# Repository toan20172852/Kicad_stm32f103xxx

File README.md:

# 1. Introduction
- Hi, I am Toan Nguyen, I learned how to using Kicad for design PCB from 1 week ago.
- I learn Kicad from some video in Youtube in [Phil'sLab](https://www.youtube.com/@PhilsLab), thank channel shared all Knowledge about Kicad for Work.
- This mini project is [course](https://www.udemy.com/course/learn-kicad-v6-and-stm32-hardware-design/learn/lecture/30585336#content) in Udemy of Phil'sLab is shared and free. If you have time, you can join the course.

# 2. Design Schematic
- **Total Schematic for STM32F103xxx**

- **Power supply:**

> I use [ASM117-3.3](https://pdf1.alldatasheet.com/datasheet-pdf/view/205691/ADMOS/AMS1117-3.3.html) as IC main for LDO voltage because:

> Current Output of ASM1117 suitable with 1A, Fixed Voltage is 3.3V for VDD of IC STM32F103.

>I using micro USB type B, current 10-100mA, Input voltage 5Vdc

>Now, we can see [example-ASM1117](https://www.pcboard.ca/ams1117-3-volt-regulator) of manafactory to design for this block:

> I using capacitor 0.1-10uF to filter input voltage, capacitor 47-1000uF to filter output voltage. LED is added to display Voltage 3.3V whether or not.

- **MCU**
> All design of MCU was referenced in internet with keyword "stm32f103c8 kit schematic", you can find schematic for this design with above keyword.

# 3. Layout
- **Layout**

- **3D**

---
---
**Goodluck!**

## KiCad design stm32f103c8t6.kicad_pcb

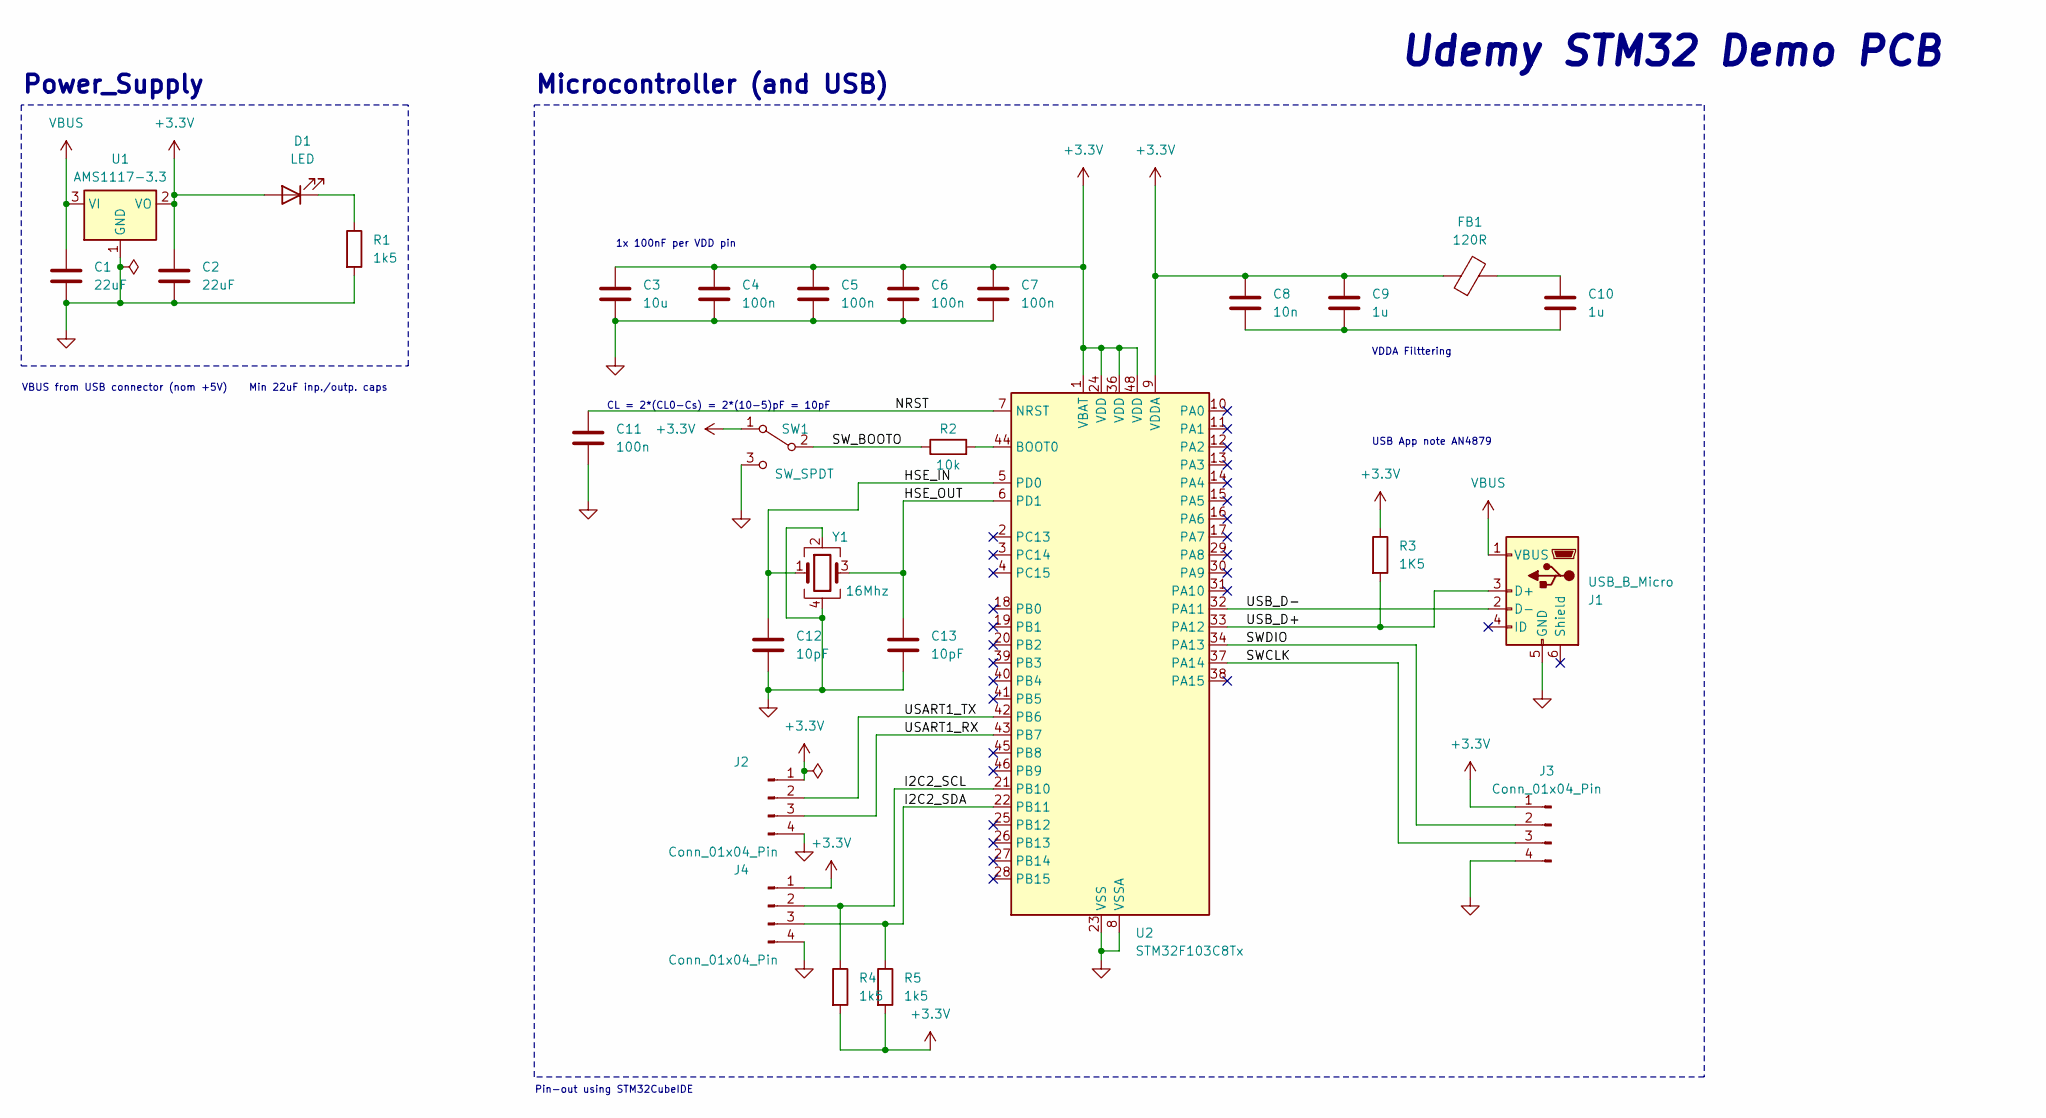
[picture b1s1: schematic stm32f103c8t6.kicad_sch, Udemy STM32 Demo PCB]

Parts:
C1, C2: 22uF; C_0805_2012Metric
C3: 10u; C_0805_2012Metric
C4, C5, C6, C7, C11: 100n; C_0402_1005Metric
C8: 10n; C_0402_1005Metric
C9, C10: 1u; C_0402_1005Metric
C12, C13: 10pF; C_0402_1005Metric
D1: LED; LED_0603_1608Metric
FB1: 120R; L_0603_1608Metric
J1: USB_B_Micro; USB_Micro-B_Wuerth_629105150521
J2, J3, J4: Conn_01x04_Pin; PinHeader_1x04_P2.54mm_Vertical
R1, R4, R5: 1k5; R_0402_1005Metric
R2: 10k; R_0402_1005Metric
R3: 1K5; R_0402_1005Metric
SW1: SW_SPDT; SW_E-Switch_EG1224_SPDT_Angled
U1: AMS1117-3.3; SOT-223-3_TabPin2
U2: STM32F103C8Tx; LQFP-48_7x7mm_P0.5mm
Y1: 16Mhz; Crystal_SMD_3225-4Pin_3.2x2.5mm

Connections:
+3.3V: C2.1, C3.1, C4.1, C5.1, C6.1, C7.1, C8.1, C9.1, D1.2 (A), FB1.1, J2.1, J3.1, J4.1, R3.1, R4.2, R5.2, SW1.1 (A), U1.2 (VO), U2.1 (VBAT), U2.9 (VDDA), U2.24 (VDD), U2.36 (VDD), U2.48 (VDD)
/HSE_IN: C12.1, U2.5 (PD0), Y1.1
/HSE_OUT: C13.1, U2.6 (PD1), Y1.3
/I2C2_SCL: J4.2, R4.1, U2.21 (PB10)
/I2C2_SDA: J4.3, R5.1, U2.22 (PB11)
/NRST: C11.1, U2.7 (NRST)
/SWCLK: J3.3, U2.37 (PA14)
/SWDIO: J3.2, U2.34 (PA13)
/SW_BOOTO: R2.1, SW1.2 (B)
/USART1_RX: J2.3, U2.43 (PB7)
/USART1_TX: J2.2, U2.42 (PB6)
/USB_D+: J1.3 (D+), R3.2, U2.33 (PA12)
/USB_D-: J1.2 (D-), U2.32 (PA11)
GND: C1.2, C2.2, C3.2, C4.2, C5.2, C6.2, C7.2, C11.2, C12.2, C13.2, J1.5 (GND), J2.4, J3.4, J4.4, R1.2, SW1.3 (C), U1.1 (GND), U2.8 (VSSA), U2.23 (VSS), U2.35 (VSS), U2.47 (VSS), Y1.2, Y1.4
unnamed: C10.1, FB1.2
unnamed: C8.2, C9.2, C10.2
unnamed: D1.1 (K), R1.1
unnamed: R2.2, U2.44 (BOOT0)
VBUS: C1.1, J1.1 (VBUS), U1.3 (VI)

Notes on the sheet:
VDDA Filttering
1x 100nF per VDD pin
Pin-out using STM32CubeIDE
USB App note AN4879
Power_Supply
CL = 2*(CL0-Cs) = 2*(10-5)pF = 10pF
VBUS from USB connector (nom +5V) Min 22uF inp./outp. caps
Microcontroller (and USB)
Udemy STM32 Demo PCB

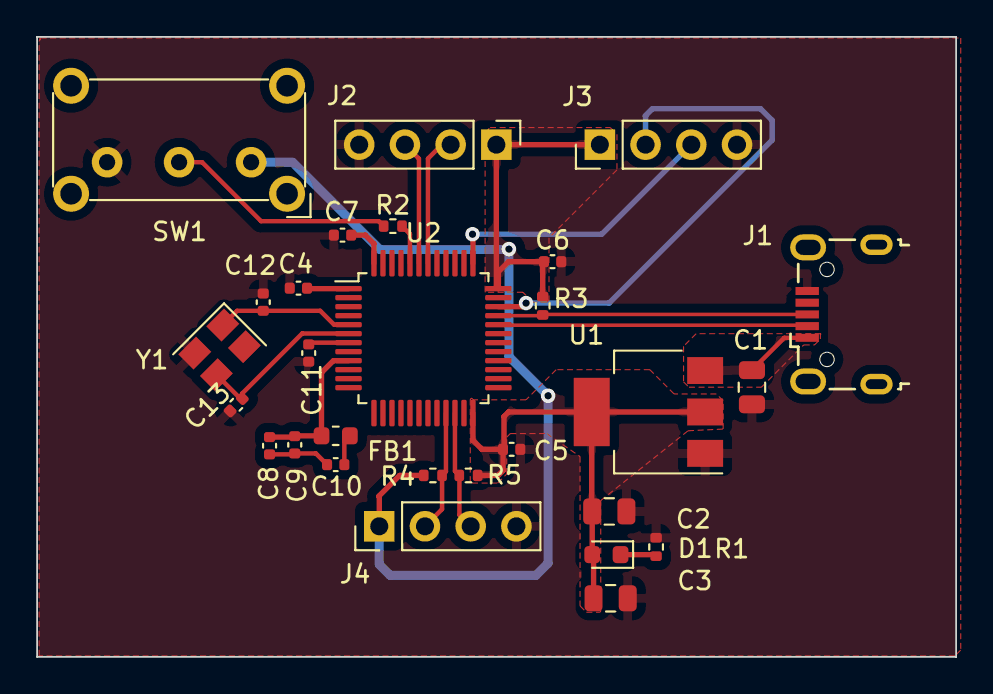
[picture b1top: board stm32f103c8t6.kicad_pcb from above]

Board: 2 copper layers, 51.1 x 34.4 mm, 28 parts (0 on the bottom side), 19 nets.

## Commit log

2023-08-06 Added KiCad fikes with CPU
2023-08-10 Add CPU and Resistor to PCB
2023-08-18 PCB Layout
2023-08-19 Layouting don't compleate
2023-09-13 stm32f103 for learn Kicad
2023-09-13 Fix font README.md
